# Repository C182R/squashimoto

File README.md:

# Squashimoto

A self-driving, self-balancing surveyor robot built from salvaged hoverboard hub motors. It roams town on its own, maps and films its route, and can stand up and balance on either wheel pair for a ~1 m camera vantage.

## Why I built this

I got my hands on a couple hoverboard motors and wanted to make the best use out of them, since I've seen so many hoverboards get thrown in the trash with perfectly good components. I wanted to help improve the community, and mapping public spaces to safely collect public data like the amount of potholes in a road or streets that get flooded in the rain, so my town knows what to fix first. It'll never directly record people or private property.

## What it does

- **Drives itself:** a Raspberry Pi 3B+ plans the route using a 2D lidar (RPLIDAR C1) and GPS.
- **Maps and films:** a Pi Camera Module 3 on a servo mount records the route.
- **Stands up and balances:** the controller board's IMU runs a balance loop on either wheel pair, which lifts the camera to about 1 m.
- **Runs on salvaged parts:** the hub motors, motor boards and center tube all come from old hoverboards.
- **Custom battery pack:** a new 10S1P pack built from Molicel P26A 18650 cells (36 V, 93.6 Wh) with a 30 A BMS. The stock hoverboard pack is only for bench testing.
- **Manual control:** drive it with a DualSense Edge controller.

## How to use it

The firmware isn't finished yet, so this is how it will work once it is.

1. **Power it on:** plug the charged battery pack into the controller board. The buzzer chirps once when the board starts up.
2. **Release the e-stop:** the robot always starts in a stopped state, and nothing moves while the e-stop is pressed.
3. **Connect the controller:** pair the DualSense Edge and arm the motors from it. If the controller disconnects or a motor board stops responding, the robot stops and has to be armed again.
4. **Drive or survey:** drive it by hand with the controller, or start a survey run on the Raspberry Pi. On a survey run it plans its own route with the lidar and GPS and records with the camera as it goes.
5. **Stand up for a higher view:** switch to balance mode so it stands up on one wheel pair and lifts the camera to about 1 m. Standing up needs the kickstand and its actuator, which aren't in the BOM yet: I left them out to save time, and the DRV8871 kickstand driver on the controller board is left unpopulated for now.
6. **Stop:** press the e-stop at any time to cut the motors.

The only optional functionality is the standing up, since the robot works perfectly fine without it.

## Pictures

| Side | Top |
|---|---|
|  |  |

## Electronics

### Controller board (`hardware/pcb/controller/`)

A 4-layer, 100 x 90 mm board that runs off the 10S battery pack (30–42 V).

- **MCU:** ESP32-WROOM-32E, with USB-C (CH340C) for flashing
- **IMU:** ICM-42688-P for the balance loop
- **Power:** a TPS54360B buck converts the 36 V pack to 5 V at 3.5 A for the Pi, the lidar and the logic. There's also a 7 A fuse, reverse-polarity protection, a TVS diode and battery voltage sensing.
- **Motor links:** three UART connectors to the hoverboard boards (one rear, two front)
- **Other I/O:** a kickstand actuator driver (DRV8871), two servo headers, a lidar connector, an encoder connector, an e-stop loop, a battery NTC, a spare Qwiic port, a WS2812B status LED and a buzzer

Schematic: [`docs/images/controller-schematic.pdf`](docs/images/controller-schematic.pdf)

### Steering encoder board (`hardware/pcb/encoder/`)

A small 2-layer AS5600 magnetic angle sensor board that reads the front swerve pivot angle. It connects to the controller over a 5-pin JST GH cable that carries I2C plus an analog output.

Schematic: [`docs/images/encoder-schematic.pdf`](docs/images/encoder-schematic.pdf)

There are two versions of this board. `encoda` is the main one, and the renders and schematic above are from it. `encoda-j1-back` is an alternate layout with the same schematic and two differences:

- **J1 is on the back:** the JST GH connector is on the bottom of the board, turned 180°, instead of on the top.
- **R1 moved:** the 100 Ω resistor on the analog output moves 7 mm to the other side of the connector, and the traces are rerouted to match.

### Drive electronics

- **Rear pair:** GD32F103 hoverboard mainboard running [EFeru hoverboard-firmware-hack-FOC](https://github.com/EFeru/hoverboard-firmware-hack-FOC), controlled over USART at 115200 baud
- **Front pair:** GD32E230 split boards running [RoboDurden Hoverboard-Firmware-Hack-Gen2.x-GD32](https://github.com/RoboDurden/Hoverboard-Firmware-Hack-Gen2.x-GD32), sharing one UART bus with a separate slave ID per board

## Repo layout

| Path | What's there |
|---|---|
| `bom/` | Bill of materials |
| `hardware/pcb/controller/` | Controller board: KiCad project and fab files (gerbers zip) |
| `hardware/pcb/encoder/` | Encoder board: KiCad project and fab files |
| `cad/` | SolidWorks parts and assemblies, plus Bambu Studio `.3mf` print projects |
| `cad/exports (STEP)/` | STEP exports of the parts and assemblies, for opening in any CAD program |
| `firmware/squashimotofirmware/` | Controller board firmware (work in progress) |
| `firmware/hoverboard/` | Notes and config for the reflashed hoverboard boards |
| `docs/images/` | Renders, schematics and CAD screenshots |
| `docs/datasheets/` | Datasheets for the parts on the boards |
| `docs/journal/` | Build journal |

## Status

V1.1 in progress. The boards and CAD are designed. The firmware is waiting on parts: it can't be tested or tuned until the boards and hoverboard hardware are here.

## License

Software (`firmware/`) is MIT. Hardware (`hardware/`, `cad/`, `bom/`, `docs/`) is CERN-OHL-S v2. See [LICENSE.md](LICENSE.md).

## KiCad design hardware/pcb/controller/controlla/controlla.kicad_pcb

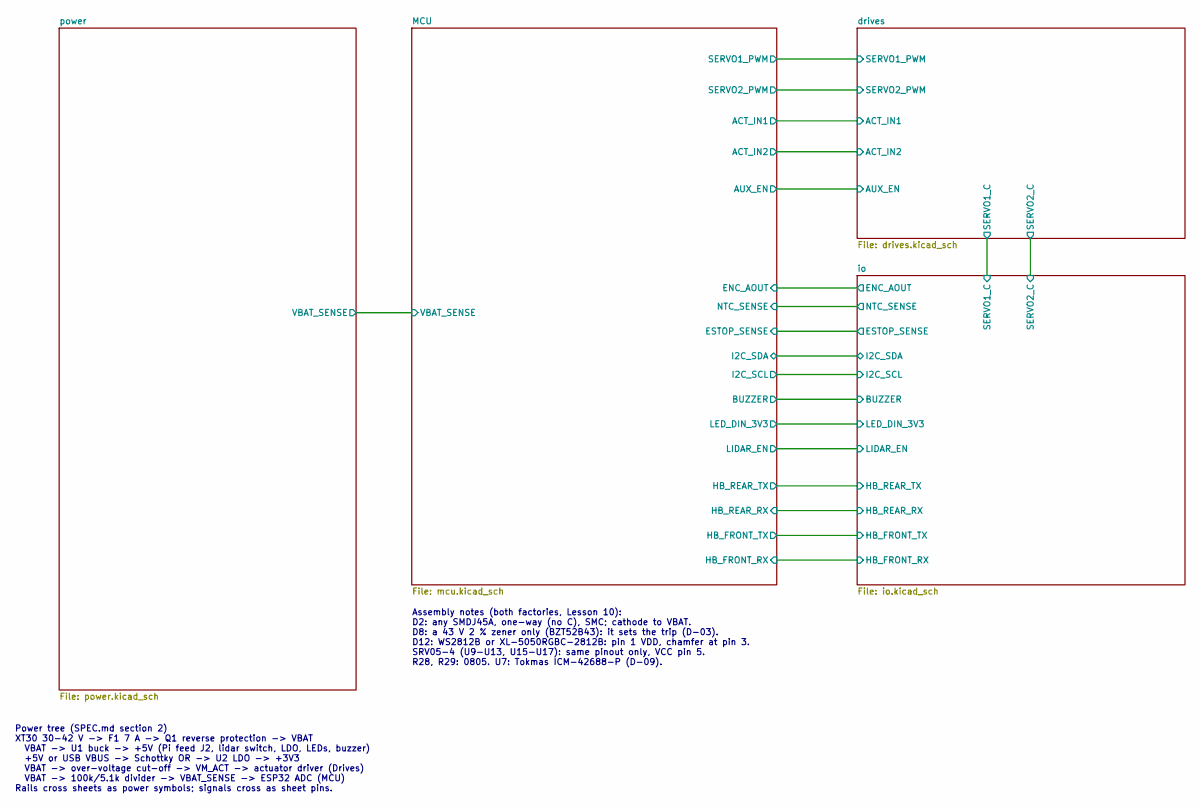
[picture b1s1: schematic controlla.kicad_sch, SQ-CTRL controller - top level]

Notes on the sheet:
Power tree (SPEC.md section 2) XT30 30-42 V -> F1 7 A -> Q1 reverse protection -> VBAT VBAT -> U1 buck -> +5V (Pi feed J2, lidar switch, LDO, LEDs, buzzer) +5V or USB VBUS -> Schottky OR -> U2 LDO -> +3V3 VBAT -> over-voltage cut-off -> VM_ACT -> actuator driver (Drives) VBAT -> 100k/5.1k divider -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
Assembly notes (both factories, Lesson 10): D2: any SMDJ45A, one-way (no C), SMC; cathode to VBAT. D8: a 43 V 2 % zener only (BZT52B43): it sets the trip (D-03). D12: WS2812B or XL-5050RGBC-2812B: pin 1 VDD, chamfer at pin 3. SRV05-4 (U9-U13, U15-U17): same pinout only, VCC pin 5. R28, R29: 0805. U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

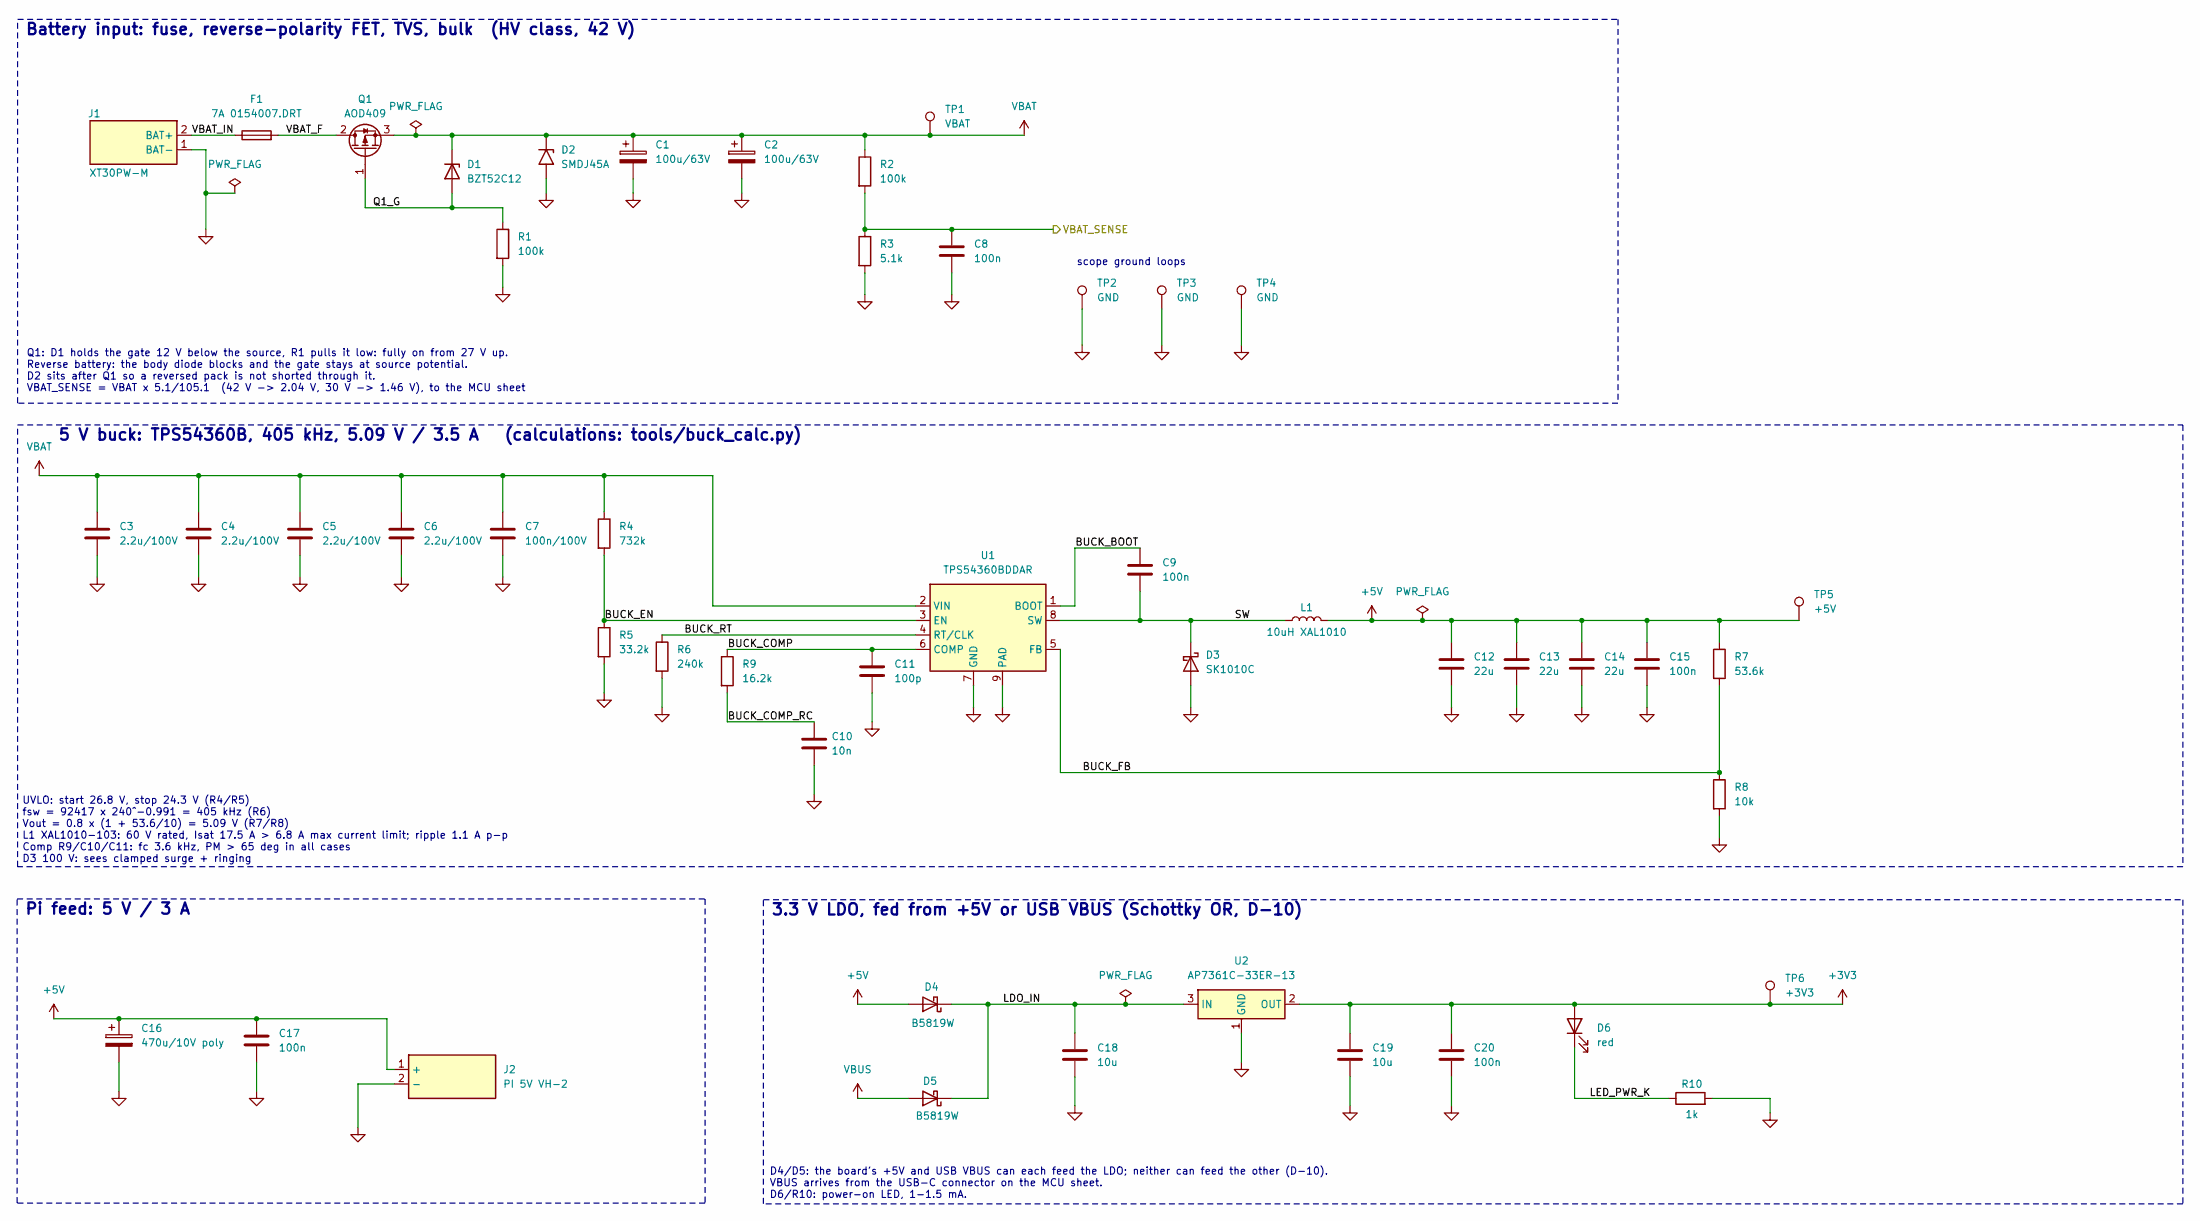
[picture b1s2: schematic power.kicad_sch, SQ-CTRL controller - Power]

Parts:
C1, C2: 100u/63V; CP_Radial_D8.0mm_P3.50mm; MPN 63ZLH100MEFC8X16; LCSC C88747
C3, C4, C5, C6: 2.2u/100V; C_1206_3216Metric; MPN CC1206KKX7R0BB225; LCSC C577211
C7: 100n/100V; C_0603_1608Metric; MPN TCC0603X7R104K101CT; LCSC C696916
C8, C9, C15, C17, C20: 100n; C_0603_1608Metric; MPN CC0603KRX7R9BB104; LCSC C14663
C10: 10n; C_0603_1608Metric; MPN CC0603KRX7R0BB103; LCSC C107059
C11: 100p; C_0603_1608Metric; MPN CL10C101JB8NNNC; LCSC C14858
C12, C13, C14: 22u; C_1206_3216Metric; MPN CL31A226KAHNNNE; LCSC C12891
C16: 470u/10V poly; CP_Radial_D6.3mm_P2.50mm; MPN SPT1AM471E08OR; LCSC C698160
C18, C19: 10u; C_0805_2012Metric; MPN CL21A106KAYNNNE; LCSC C15850
D1: BZT52C12; D_SOD-123; MPN BZT52C12; LCSC C173429
D2: SMDJ45A; D_SMC; MPN SMDJ45A; LCSC C49066976
D3: SK1010C; D_SMC; MPN SK1010C; LCSC C65020
D4, D5: B5819W; D_SOD-123; MPN B5819W; LCSC C64885
D6: red; LED_0603_1608Metric; MPN KT-0603R; LCSC C2286
F1: 7A 0154007.DRT; Fuseholder_Littelfuse_Nano2_154x; MPN 0154007.DRT; LCSC C2760740
J1: XT30PW-M; AMASS_XT30PW-M_1x02_P2.50mm_Horizontal; MPN XT30PW-M30.G.Y; LCSC C431092
J2: PI 5V VH-2; JST_VH_B2P-VH_1x02_P3.96mm_Vertical; MPN B2P-VH(LF)(SN); LCSC C160315
L1: 10uH XAL1010; L_Coilcraft_XAL1010-XXX; MPN XAL1010-103MED; LCSC C6358489
Q1: AOD409; TO-252-2; MPN AOD409; LCSC C36220
R1, R2: 100k; R_0603_1608Metric; MPN 0603WAF1003T5E; LCSC C25803
R3: 5.1k; R_0603_1608Metric; MPN 0603WAF5101T5E; LCSC C23186
R4: 732k; R_0603_1608Metric; MPN 0603WAF7323T5E; LCSC C23239
R5: 33.2k; R_0603_1608Metric; MPN 0603WAF3322T5E; LCSC C23003
R6: 240k; R_0603_1608Metric; MPN 0603WAF2403T5E; LCSC C4197
R7: 53.6k; R_0603_1608Metric; MPN 0603WAF5362T5E; LCSC C23074
R8: 10k; R_0603_1608Metric; MPN 0603WAF1002T5E; LCSC C25804
R9: 16.2k; R_0603_1608Metric; MPN 0603WAF1622T5E; LCSC C22885
R10: 1k; R_0603_1608Metric; MPN 0603WAF1001T5E; LCSC C21190
TP1: VBAT; TestPoint_Pad_D1.5mm
TP2, TP3, TP4: GND; TestPoint_Loop_D2.50mm_Drill1.0mm
TP5: +5V; TestPoint_Pad_D1.5mm
TP6: +3V3; TestPoint_Pad_D1.5mm
U1: TPS54360BDDAR; HSOP-8-1EP_3.9x4.9mm_P1.27mm_EP2.41x3.1mm; MPN TPS54360BDDAR; LCSC C524806
U2: AP7361C-33ER-13; SOT-223-3_TabPin2; MPN AP7361C-33ER-13; LCSC C3743528

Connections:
+3V3: C19.1, C20.1, D6.2 (A), TP6.1 (1_1), U2.2 (OUT); also elsewhere on the board
+5V: C12.1, C13.1, C14.1, C15.1, C16.1, C17.1, D4.2 (A), J2.1 (+), L1.2, R7.1, TP5.1 (1_1); also elsewhere on the board
/MCU/VBAT_SENSE: C8.1, R2.2, R3.1; also elsewhere on the board
/power/BUCK_BOOT: C9.1, U1.1 (BOOT)
/power/BUCK_COMP: C11.1, R9.1, U1.6 (COMP)
/power/BUCK_COMP_RC: C10.1, R9.2
/power/BUCK_EN: R4.2, R5.1, U1.3 (EN)
/power/BUCK_FB: R7.2, R8.1, U1.5 (FB)
/power/BUCK_RT: R6.1, U1.4 (RT/CLK)
/power/LDO_IN: C18.1, D4.1 (K), D5.1 (K), U2.3 (IN)
/power/LED_PWR_K: D6.1 (K), R10.1
/power/Q1_G: D1.2 (A), Q1.1 (G), R1.1
/power/SW: C9.2, D3.1 (K), L1.1, U1.8 (SW)
/power/VBAT_F: F1.2, Q1.2 (D)
/power/VBAT_IN: F1.1, J1.2 (BAT+)
GND: C1.2, C2.2, C3.2, C4.2, C5.2, C6.2, C7.2, C8.2, C10.2, C11.2, C12.2, C13.2, C14.2, C15.2, C16.2, C17.2, C18.2, C19.2, C20.2, D2.2 (A2), D3.2 (A), J1.1 (BAT-), J2.2 (-), R1.2, R3.2, R5.2, R6.2, R8.2, R10.2, TP2.1 (1_1), TP3.1 (1_1), TP4.1 (1_1), U1.7 (GND), U1.9 (PAD), U2.1 (GND); also elsewhere on the board
VBAT: C1.1, C2.1, C3.1, C4.1, C5.1, C6.1, C7.1, D1.1 (K), D2.1 (A1), Q1.3 (S), R2.1, R4.1, TP1.1 (1_1), U1.2 (VIN); also elsewhere on the board
VBUS: D5.2 (A); also elsewhere on the board

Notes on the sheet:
Pi feed: 5 V / 3 A
D4/D5: the board's +5V and USB VBUS can each feed the LDO; neither can feed the other (D-10). VBUS arrives from the USB-C connector on the MCU sheet. D6/R10: power-on LED, 1-1.5 mA.
Q1: D1 holds the gate 12 V below the source, R1 pulls it low: fully on from 27 V up. Reverse battery: the body diode blocks and the gate stays at source potential. D2 sits after Q1 so a reversed pack is not shorted through it. VBAT_SENSE = VBAT x 5.1/105.1 (42 V -> 2.04 V, 30 V -> 1.46 V), to the M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
3.3 V LDO, fed from +5V or USB VBUS (Schottky OR, D-10)
scope ground loops
UVLO: start 26.8 V, stop 24.3 V (R4/R5) fsw = 92417 x 240^-0.991 = 405 kHz (R6) Vout = 0.8 x (1 + 53.6/10) = 5.09 V (R7/R8) L1 XAL1010-103: 60 V rated, Isat 17.5 A > 6.8 A max current limit; ripple 1.1 A p-p Comp R9/C10/C11: fc 3.6 kHz, PM > 65 deg in all cases D3 100 V: sees clamped surge + ringing
Battery input: fuse, reverse-polarity FET, TVS, bulk (HV class, 42 V)
5 V buck: TPS54360B, 405 kHz, 5.09 V / 3.5 A (calculations: tools/buck_calc.py)

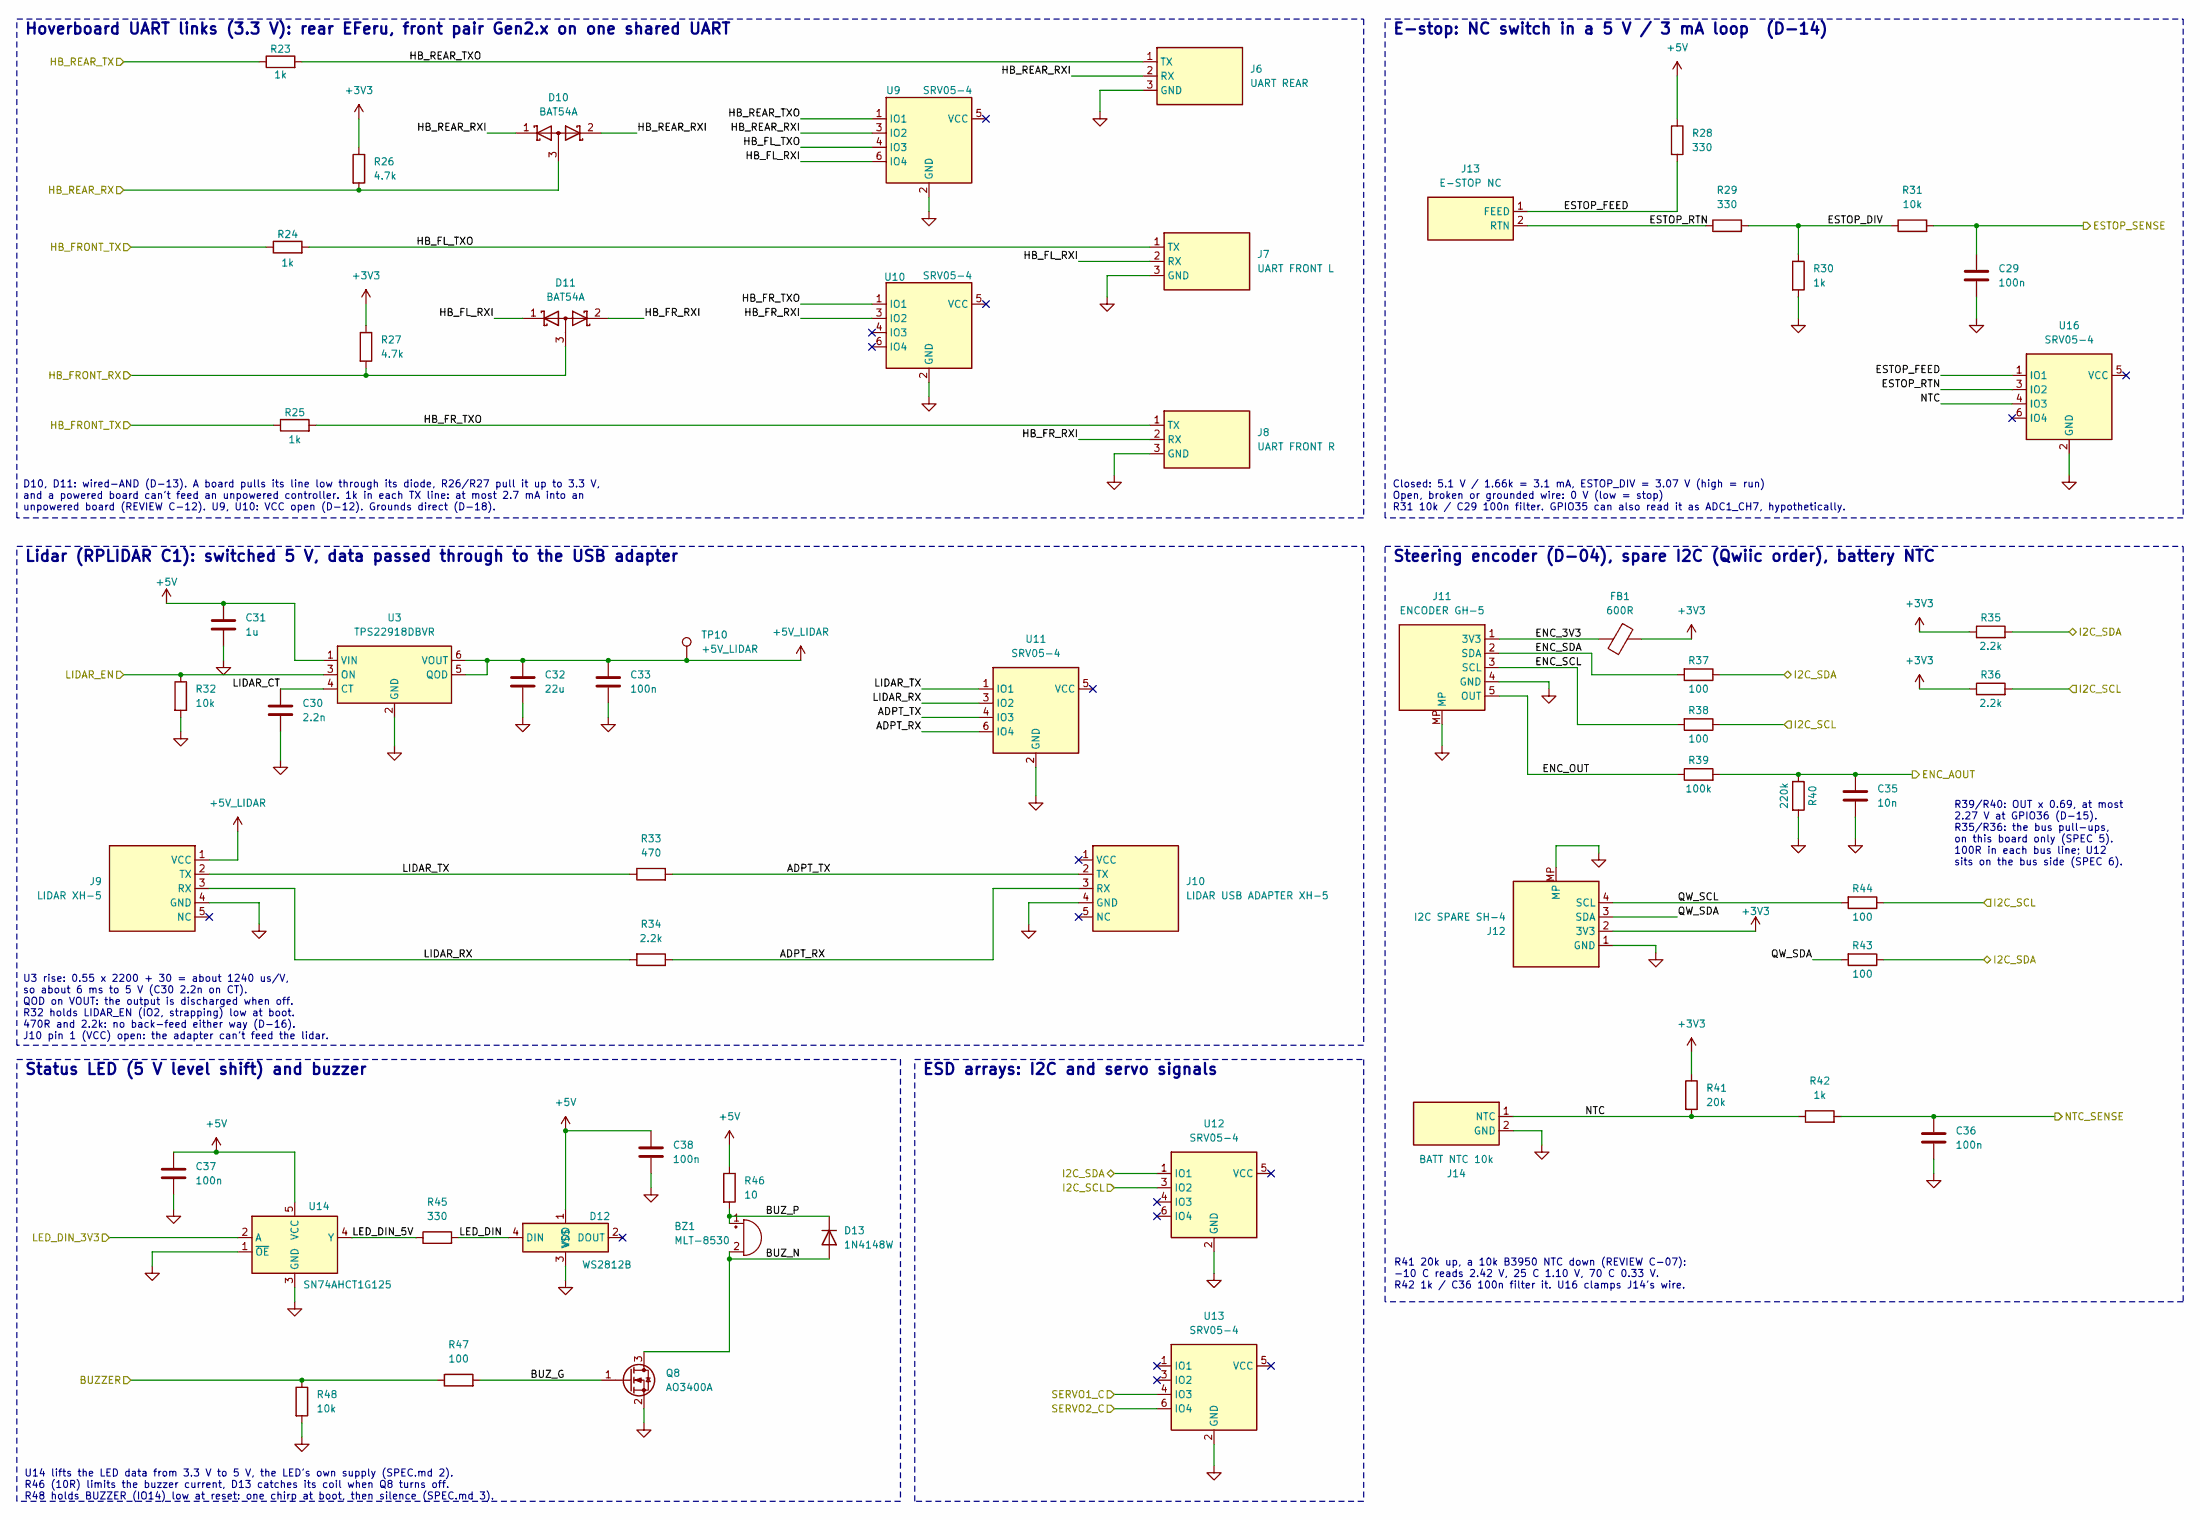
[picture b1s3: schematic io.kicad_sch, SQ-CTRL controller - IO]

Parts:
BZ1: MLT-8530; Buzzer_Huaneng_MLT-8530; MPN MLT-8530; LCSC C94599
C29, C33, C36, C37, C38: 100n; C_0603_1608Metric; MPN CC0603KRX7R9BB104; LCSC C14663
C30: 2.2n; C_0603_1608Metric; MPN CL10B222KB8NNNC; LCSC C16033
C31: 1u; C_0603_1608Metric; MPN CL10A105KB8NNNC; LCSC C15849
C32: 22u; C_1206_3216Metric; MPN CL31A226KAHNNNE; LCSC C12891
C35: 10n; C_0603_1608Metric; MPN CC0603KRX7R0BB103; LCSC C107059
D10, D11: BAT54A; SOT-23; MPN BAT54A; LCSC C181199
D12: WS2812B; LED_WS2812B_PLCC4_5.0x5.0mm_P3.2mm; MPN XL-5050RGBC-2812B; LCSC C2843785
D13: 1N4148W; D_SOD-123; MPN 1N4148W; LCSC C81598
FB1: 600R; L_0603_1608Metric; MPN BLM18AG601SN1D; LCSC C19330
J6: UART REAR; JST_XH_B3B-XH-A_1x03_P2.50mm_Vertical; MPN B3B-XH-A(LF)(SN); LCSC C144394
J7: UART FRONT L; JST_XH_B3B-XH-A_1x03_P2.50mm_Vertical; MPN B3B-XH-A(LF)(SN); LCSC C144394
J8: UART FRONT R; JST_XH_B3B-XH-A_1x03_P2.50mm_Vertical; MPN B3B-XH-A(LF)(SN); LCSC C144394
J9: LIDAR XH-5; JST_XH_B5B-XH-A_1x05_P2.50mm_Vertical; MPN B5B-XH-A(LF)(SN); LCSC C157991
J10: LIDAR USB ADAPTER XH-5; JST_XH_B5B-XH-A_1x05_P2.50mm_Vertical; MPN B5B-XH-A(LF)(SN); LCSC C157991
J11: ENCODER GH-5; JST_GH_SM05B-GHS-TB_1x05-1MP_P1.25mm_Horizontal; MPN SM05B-GHS-TB(LF)(SN); LCSC C189896
J12: I2C SPARE SH-4; JST_SH_SM04B-SRSS-TB_1x04-1MP_P1.00mm_Horizontal; MPN SM04B-SRSS-TB(LF)(SN); LCSC C160404
J13: E-STOP NC; JST_XH_B2B-XH-A_1x02_P2.50mm_Vertical; MPN B2B-XH-A(LF)(SN); LCSC C158012
J14: BATT NTC 10k; JST_XH_B2B-XH-A_1x02_P2.50mm_Vertical; MPN B2B-XH-A(LF)(SN); LCSC C158012
Q8: AO3400A; SOT-23; MPN AO3400A; LCSC C20917
R23, R24, R25, R30, R42: 1k; R_0603_1608Metric; MPN 0603WAF1001T5E; LCSC C21190
R26, R27: 4.7k; R_0603_1608Metric; MPN 0603WAF4701T5E; LCSC C23162
R28, R29: 330; R_0805_2012Metric; MPN 0805W8F3300T5E; LCSC C17630
R31, R32, R48: 10k; R_0603_1608Metric; MPN 0603WAF1002T5E; LCSC C25804
R33: 470; R_0603_1608Metric; MPN 0603WAF4700T5E; LCSC C23179
R34, R35, R36: 2.2k; R_0603_1608Metric; MPN 0603WAF2201T5E; LCSC C4190
R37, R38, R43, R44, R47: 100; R_0603_1608Metric; MPN 0603WAF1000T5E; LCSC C22775
R39: 100k; R_0603_1608Metric; MPN 0603WAF1003T5E; LCSC C25803
R40: 220k; R_0603_1608Metric; MPN 0603WAF2203T5E; LCSC C22961
R41: 20k; R_0603_1608Metric; MPN 0603WAF2002T5E; LCSC C4184
R45: 330; R_0603_1608Metric; MPN 0603WAF3300T5E; LCSC C23138
R46: 10; R_1206_3216Metric; MPN 1206W4F100JT5E; LCSC C17903
TP10: +5V_LIDAR; TestPoint_Pad_D1.5mm
U3: TPS22918DBVR; SOT-23-6; MPN TPS22918DBVR; LCSC C131941
U9, U10, U11, U12, U13, U16: SRV05-4; SOT-23-6; MPN SRV05-4; LCSC C558418
U14: SN74AHCT1G125; SOT-23-5; MPN SN74AHCT1G125DBVR; LCSC C7484

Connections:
+3V3: FB1.1, J12.2 (3V3), R26.1, R27.1, R35.1, R36.1, R41.1; also elsewhere on the board
+5V: C31.1, C37.1, C38.1, D12.1 (VDD), R28.1, R46.1, U3.1 (VIN), U14.5 (VCC); also elsewhere on the board
+5V_LIDAR: C32.1, C33.1, J9.1 (VCC), TP10.1 (1_1), U3.5 (QOD), U3.6 (VOUT)
/MCU/BUZZER: R47.1, R48.1; also elsewhere on the board
/MCU/ENC_AOUT: C35.1, R39.2, R40.1; also elsewhere on the board
/MCU/ESTOP_SENSE: C29.1, R31.2; also elsewhere on the board
/MCU/HB_FRONT_RX: D11.3 (A), R27.2; also elsewhere on the board
/MCU/HB_FRONT_TX: R24.1, R25.1; also elsewhere on the board
/MCU/HB_REAR_RX: D10.3 (A), R26.2; also elsewhere on the board
/MCU/HB_REAR_TX: R23.1; also elsewhere on the board
/MCU/I2C_SCL: R36.2, R38.1, R44.1, U12.3 (IO2); also elsewhere on the board
/MCU/I2C_SDA: R35.2, R37.1, R43.1, U12.1 (IO1); also elsewhere on the board
/MCU/LED_DIN_3V3: U14.2 (A); also elsewhere on the board
/MCU/LIDAR_EN: R32.1, U3.3 (ON); also elsewhere on the board
/MCU/NTC_SENSE: C36.1, R42.2; also elsewhere on the board
/drives/SERVO1_C: U13.4 (IO3); also elsewhere on the board
/drives/SERVO2_C: U13.6 (IO4); also elsewhere on the board
/io/ADPT_RX: J10.3 (RX), R34.1, U11.6 (IO4)
/io/ADPT_TX: J10.2 (TX), R33.2, U11.4 (IO3)
/io/BUZ_G: Q8.1 (G), R47.2
/io/BUZ_N: BZ1.2 (-), D13.2 (A), Q8.3 (D)
/io/BUZ_P: BZ1.1 (+), D13.1 (K), R46.2
/io/ENC_3V3: FB1.2, J11.1 (3V3)
/io/ENC_OUT: J11.5 (OUT), R39.1
/io/ENC_SCL: J11.3 (SCL), R38.2
/io/ENC_SDA: J11.2 (SDA), R37.2
/io/ESTOP_DIV: R29.2, R30.1, R31.1
/io/ESTOP_FEED: J13.1 (FEED), R28.2, U16.1 (IO1)
/io/ESTOP_RTN: J13.2 (RTN), R29.1, U16.3 (IO2)
/io/HB_FL_RXI: D11.1 (K), J7.2 (RX), U9.6 (IO4)
/io/HB_FL_TXO: J7.1 (TX), R24.2, U9.4 (IO3)
/io/HB_FR_RXI: D11.2 (K), J8.2 (RX), U10.3 (IO2)
/io/HB_FR_TXO: J8.1 (TX), R25.2, U10.1 (IO1)
/io/HB_REAR_RXI: D10.1 (K), D10.2 (K), J6.2 (RX), U9.3 (IO2)
/io/HB_REAR_TXO: J6.1 (TX), R23.2, U9.1 (IO1)
/io/LED_DIN: D12.4 (DIN), R45.2
/io/LED_DIN_5V: R45.1, U14.4 (Y)
/io/LIDAR_CT: C30.1, U3.4 (CT)
/io/LIDAR_RX: J9.3 (RX), R34.2, U11.3 (IO2)
/io/LIDAR_TX: J9.2 (TX), R33.1, U11.1 (IO1)
/io/NTC: J14.1 (NTC), R41.2, R42.1, U16.4 (IO3)
/io/QW_SCL: J12.4 (SCL), R44.2
/io/QW_SDA: J12.3 (SDA), R43.2
GND: C29.2, C30.2, C31.2, C32.2, C33.2, C35.2, C36.2, C37.2, C38.2, D12.3 (VSS), J6.3 (GND), J7.3 (GND), J8.3 (GND), J9.4 (GND), J10.4 (GND), J11.4 (GND), J11.MP, J12.1 (GND), J12.MP, J14.2 (GND), Q8.2 (S), R30.2, R32.2, R40.2, R48.2, U3.2 (GND), U9.2 (GND), U10.2 (GND), U11.2 (GND), U12.2 (GND), U13.2 (GND), U14.1 (~OE), U14.3 (GND), U16.2 (GND); also elsewhere on the board

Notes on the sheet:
ESD arrays: I2C and servo signals
U14 lifts the LED data from 3.3 V to 5 V, the LED's own supply (SPEC.md 2). R46 (10R) limits the buzzer current, D13 catches its coil when Q8 turns off. R48 holds BUZZER (IO14) low at reset: one chirp at boot, then silence (SPEC.md 3).
Status LED (5 V level shift) and buzzer
Steering encoder (D-04), spare I2C (Qwiic order), battery NTC
Hoverboard UART links (3.3 V): rear EFeru, front pair Gen2.x on one shared UART
Closed: 5.1 V / 1.66k = 3.1 mA, ESTOP_DIV = 3.07 V (high = run) Open, broken or grounded wire: 0 V (low = stop) R31 10k / C29 100n filter. GPIO35 can also read it as ADC1_CH7, hypothetically.
Lidar (RPLIDAR C1): switched 5 V, data passed through to the USB adapter
E-stop: NC switch in a 5 V / 3 mA loop (D-14)
U3 rise: 0.55 x 2200 + 30 = about 1240 us/V, so about 6 ms to 5 V (C30 2.2n on CT). QOD on VOUT: the output is discharged when off. R32 holds LIDAR_EN (IO2, strapping) low at boot. 470R and 2.2k: no back-feed either way (D-16). J10 pin 1 (VCC) open: the adapter can't feed the lidar.
R41 20k up, a 10k B3950 NTC down (REVIEW C-07): -10 C reads 2.42 V, 25 C 1.10 V, 70 C 0.33 V. R42 1k / C36 100n filter it. U16 clamps J14's wire.
R39/R40: OUT x 0.69, at most 2.27 V at GPIO36 (D-15). R35/R36: the bus pull-ups, on this board only (SPEC 5). 100R in each bus line; U12 sits on the bus side (SPEC 6).
D10, D11: wired-AND (D-13). A board pulls its line low through its diode, R26/R27 pull it up to 3.3 V, and a powered board can't feed an unpowered controller. 1k in each TX line: at most 2.7 mA into an unpowered board (REVIEW C-12). U9, U10: VCC open (D-12). Grounds direct (D-18).

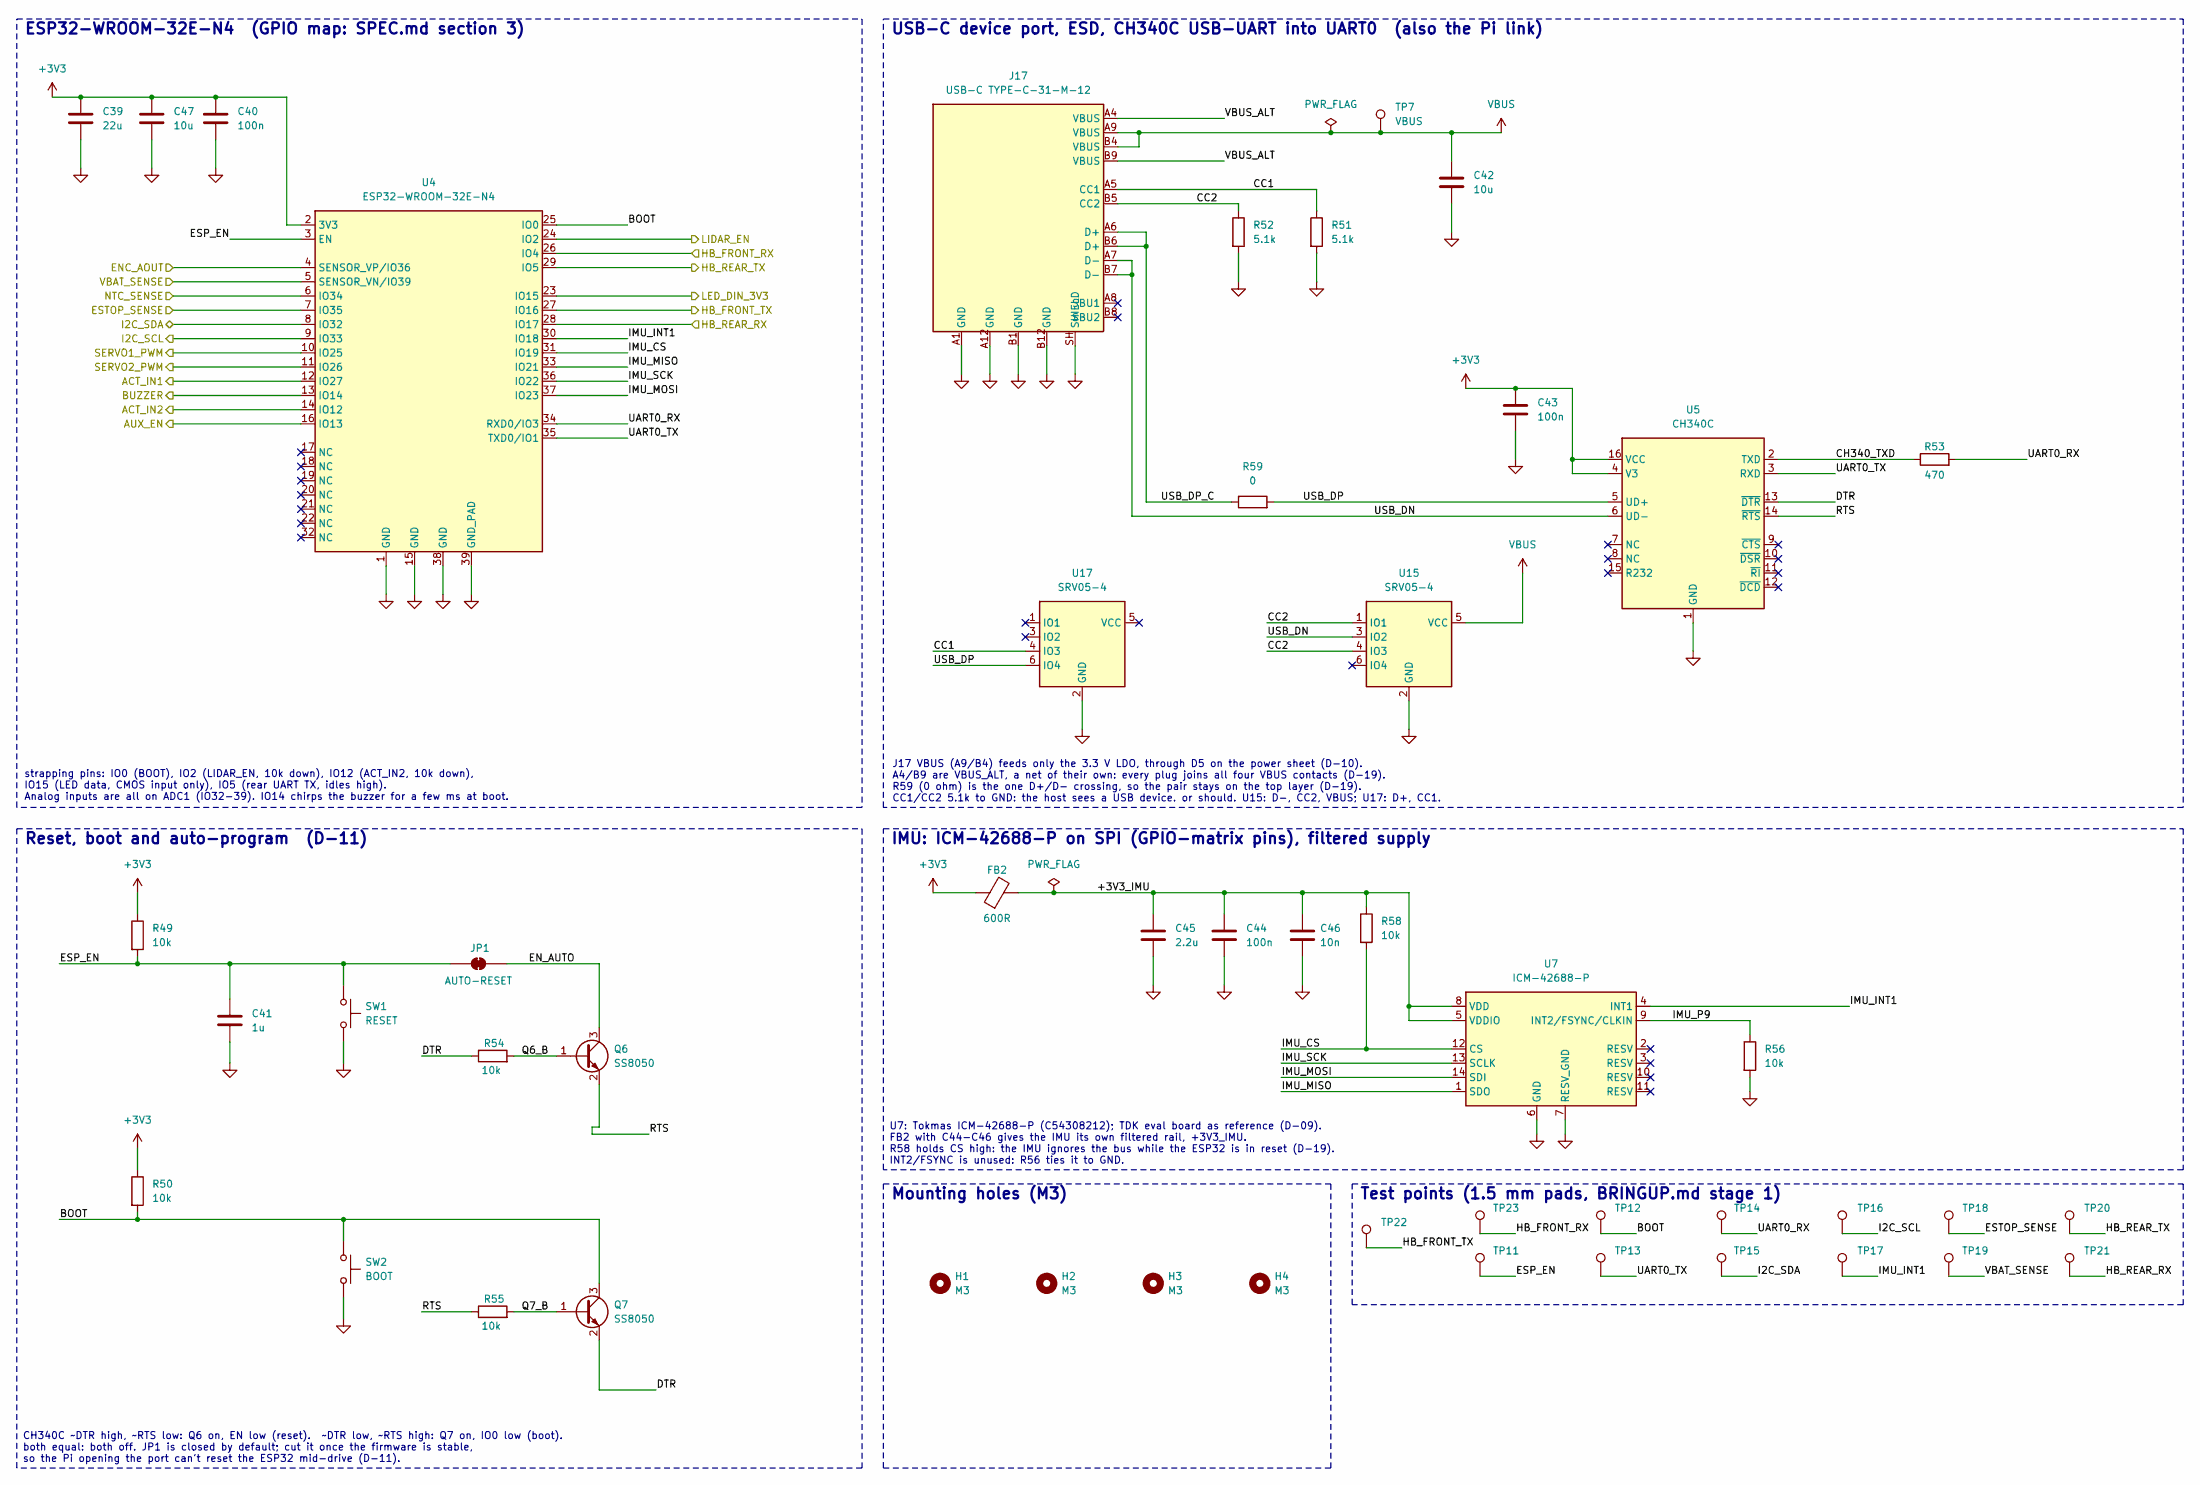
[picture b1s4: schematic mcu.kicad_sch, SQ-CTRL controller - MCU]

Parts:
C39: 22u; C_1206_3216Metric; MPN CL31A226KAHNNNE; LCSC C12891
C40, C43, C44: 100n; C_0603_1608Metric; MPN CC0603KRX7R9BB104; LCSC C14663
C41: 1u; C_0603_1608Metric; MPN CL10A105KB8NNNC; LCSC C15849
C42, C47: 10u; C_0805_2012Metric; MPN CL21A106KAYNNNE; LCSC C15850
C45: 2.2u; C_0603_1608Metric; MPN CL10A225KO8NNNC; LCSC C23630
C46: 10n; C_0603_1608Metric; MPN CC0603KRX7R0BB103; LCSC C107059
FB2: 600R; L_0603_1608Metric; MPN BLM18AG601SN1D; LCSC C19330
H1, H2, H3, H4: M3; MountingHole_3.2mm_M3
J17: USB-C TYPE-C-31-M-12; USB_C_Receptacle_HRO_TYPE-C-31-M-12; MPN TYPE-C-31-M-12; LCSC C165948
JP1: AUTO-RESET; SolderJumper-2_P1.3mm_Bridged_RoundedPad1.0x1.5mm
Q6, Q7: SS8050; SOT-23; MPN SS8050(RANGE:200-350); LCSC C2150
R49, R50, R54, R55, R56, R58: 10k; R_0603_1608Metric; MPN 0603WAF1002T5E; LCSC C25804
R51, R52: 5.1k; R_0603_1608Metric; MPN 0603WAF5101T5E; LCSC C23186
R53: 470; R_0603_1608Metric; MPN 0603WAF4700T5E; LCSC C23179
R59: 0; R_0603_1608Metric; MPN 0603WAF0000T5E; LCSC C21189
SW1: RESET; SW_Push_1P1T_XKB_TS-1187A; MPN TS-1187A-B-A-B; LCSC C318884
SW2: BOOT; SW_Push_1P1T_XKB_TS-1187A; MPN TS-1187A-B-A-B; LCSC C318884
TP7: VBUS; TestPoint_Pad_D1.5mm
TP11: ESP_EN; TestPoint_Pad_D1.5mm
TP12: BOOT; TestPoint_Pad_D1.5mm
TP13: UART0_TX; TestPoint_Pad_D1.5mm
TP14: UART0_RX; TestPoint_Pad_D1.5mm
TP15: I2C_SDA; TestPoint_Pad_D1.5mm
TP16: I2C_SCL; TestPoint_Pad_D1.5mm
TP17: IMU_INT1; TestPoint_Pad_D1.5mm
TP18: ESTOP_SENSE; TestPoint_Pad_D1.5mm
TP19: VBAT_SENSE; TestPoint_Pad_D1.5mm
TP20: HB_REAR_TX; TestPoint_Pad_D1.5mm
TP21: HB_REAR_RX; TestPoint_Pad_D1.5mm
TP22: HB_FRONT_TX; TestPoint_Pad_D1.5mm
TP23: HB_FRONT_RX; TestPoint_Pad_D1.5mm
U4: ESP32-WROOM-32E-N4; ESP32-WROOM-32E; MPN ESP32-WROOM-32E-N4; LCSC C701341
U5: CH340C; SOIC-16_3.9x9.9mm_P1.27mm; MPN CH340C; LCSC C84681
U7: ICM-42688-P; LGA-14_3x2.5mm_P0.5mm_ICM-42688-P; MPN ICM-42688-P(TOKMAS); LCSC C54308212
U15, U17: SRV05-4; SOT-23-6; MPN SRV05-4; LCSC C558418

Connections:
+3V3: C39.1, C40.1, C43.1, C47.1, FB2.1, R49.1, R50.1, U4.2 (3V3), U5.4 (V3), U5.16 (VCC); also elsewhere on the board
/MCU/+3V3_IMU: C44.1, C45.1, C46.1, FB2.2, R58.1, U7.5 (VDDIO), U7.8 (VDD)
/MCU/ACT_IN1: U4.12 (IO27); also elsewhere on the board
/MCU/ACT_IN2: U4.14 (IO12); also elsewhere on the board
/MCU/AUX_EN: U4.16 (IO13); also elsewhere on the board
/MCU/BOOT: Q7.3 (C), R50.2, SW2.1, TP12.1 (1_1), U4.25 (IO0)
/MCU/BUZZER: U4.13 (IO14); also elsewhere on the board
/MCU/CC1: J17.A5 (CC1), R51.1, U17.4 (IO3)
/MCU/CC2: J17.B5 (CC2), R52.1, U15.1 (IO1), U15.4 (IO3)
/MCU/CH340_TXD: R53.1, U5.2 (TXD)
/MCU/DTR: Q7.2 (E), R54.1, U5.13 (~DTR)
/MCU/ENC_AOUT: U4.4 (SENSOR_VP/IO36); also elsewhere on the board
/MCU/EN_AUTO: JP1.1 (A), Q6.3 (C)
/MCU/ESP_EN: C41.1, JP1.2 (B), R49.2, SW1.1, TP11.1 (1_1), U4.3 (EN)
/MCU/ESTOP_SENSE: TP18.1 (1_1), U4.7 (IO35); also elsewhere on the board
/MCU/HB_FRONT_RX: TP23.1 (1_1), U4.26 (IO4); also elsewhere on the board
/MCU/HB_FRONT_TX: TP22.1 (1_1), U4.27 (IO16); also elsewhere on the board
/MCU/HB_REAR_RX: TP21.1 (1_1), U4.28 (IO17); also elsewhere on the board
/MCU/HB_REAR_TX: TP20.1 (1_1), U4.29 (IO5); also elsewhere on the board
/MCU/I2C_SCL: TP16.1 (1_1), U4.9 (IO33); also elsewhere on the board
/MCU/I2C_SDA: TP15.1 (1_1), U4.8 (IO32); also elsewhere on the board
/MCU/IMU_CS: R58.2, U4.31 (IO19), U7.12 (CS)
/MCU/IMU_INT1: TP17.1 (1_1), U4.30 (IO18), U7.4 (INT1)
/MCU/IMU_MISO: U4.33 (IO21), U7.1 (SDO)
/MCU/IMU_MOSI: U4.37 (IO23), U7.14 (SDI)
/MCU/IMU_P9: R56.1, U7.9 (INT2/FSYNC/CLKIN)
/MCU/IMU_SCK: U4.36 (IO22), U7.13 (SCLK)
/MCU/LED_DIN_3V3: U4.23 (IO15); also elsewhere on the board
/MCU/LIDAR_EN: U4.24 (IO2); also elsewhere on the board
/MCU/NTC_SENSE: U4.6 (IO34); also elsewhere on the board
/MCU/Q6_B: Q6.1 (B), R54.2
/MCU/Q7_B: Q7.1 (B), R55.2
/MCU/RTS: Q6.2 (E), R55.1, U5.14 (~RTS)
/MCU/SERVO1_PWM: U4.10 (IO25); also elsewhere on the board
/MCU/SERVO2_PWM: U4.11 (IO26); also elsewhere on the board
/MCU/UART0_RX: R53.2, TP14.1 (1_1), U4.34 (RXD0/IO3)
/MCU/UART0_TX: TP13.1 (1_1), U4.35 (TXD0/IO1), U5.3 (RXD)
/MCU/USB_DN: J17.A7 (D-), J17.B7 (D-), U5.6 (UD-), U15.3 (IO2)
/MCU/USB_DP: R59.2, U5.5 (UD+), U17.6 (IO4)
/MCU/USB_DP_C: J17.A6 (D+), J17.B6 (D+), R59.1
/MCU/VBAT_SENSE: TP19.1 (1_1), U4.5 (SENSOR_VN/IO39); also elsewhere on the board
/MCU/VBUS_ALT: J17.A4 (VBUS), J17.B9 (VBUS)
GND: C39.2, C40.2, C41.2, C42.2, C43.2, C44.2, C45.2, C46.2, C47.2, J17.A1 (GND), J17.A12 (GND), J17.B1 (GND), J17.B12 (GND), J17.SH (SHIELD), R51.2, R52.2, R56.2, SW1.2, SW2.2, U4.1 (GND), U4.15 (GND), U4.38 (GND), U4.39 (GND_PAD), U5.1 (GND), U7.6 (GND), U7.7 (RESV_GND), U15.2 (GND), U17.2 (GND); also elsewhere on the board
VBUS: C42.1, J17.A9 (VBUS), J17.B4 (VBUS), TP7.1 (1_1), U15.5 (VCC); also elsewhere on the board

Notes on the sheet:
U7: Tokmas ICM-42688-P (C54308212); TDK eval board as reference (D-09). FB2 with C44-C46 gives the IMU its own filtered rail, +3V3_IMU. R58 holds CS high: the IMU ignores the bus while the ESP32 is in reset (D-19). INT2/FSYNC is unused: R56 ties it to GND.
ESP32-WROOM-32E-N4 (GPIO map: SPEC.md section 3)
strapping pins: IO0 (BOOT), IO2 (LIDAR_EN, 10k down), IO12 (ACT_IN2, 10k down), IO15 (LED data, CMOS input only), IO5 (rear UART TX, idles high). Analog inputs are all on ADC1 (IO32-39). IO14 chirps the buzzer for a few ms at boot.
J17 VBUS (A9/B4) feeds only the 3.3 V LDO, through D5 on the power sheet (D-10). A4/B9 are VBUS_ALT, a net of their own: every plug joins all four VBUS contacts (D-19). R59 (0 ohm) is the one D+/D- crossing, so the pair stays on the top layer (D-19). CC1/CC2 5.1k to GND: the host sees a USB device.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
CH340C ~DTR high, ~RTS low: Q6 on, EN low (reset). ~DTR low, ~RTS high: Q7 on, IO0 low (boot). both equal: both off. JP1 is closed by default; cut it once the firmware is stable, so the Pi opening the port can't reset the ESP32 mid-drive (D-11).
Reset, boot and auto-program (D-11)
USB-C device port, ESD, CH340C USB-UART into UART0 (also the Pi link)
IMU: ICM-42688-P on SPI (GPIO-matrix pins), filtered supply
Test points (1.5 mm pads, BRINGUP.md stage 1)
Mounting holes (M3)
